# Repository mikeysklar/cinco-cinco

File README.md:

# Cinco-Cinco  
*A 5-Key Wireless Chording Keyboard*

Cinco-Cinco is a low-profile chording keyboard that uses just **five
keys** to emulate a full keyboard by combining keypresses into
chords and utilizing **seven layers**.

I’ve spent the last year building pocket keyboards. My
[BUBBY](https://github.com/mikeysklar/bubby) is a daily carry which
I use for todo lists. It made me enjoy typing with one hand to the
point that I wanted a desktop version, which is what you see here.

## Table of Contents

- [Introduction](#introduction)
- [Hardware Highlights](#hardware-highlights)
  - [Case Design](#case-design)
  - [Mechanical Switch Choice](#mechanical-switch-choice)
  - [Chording Software](#chording-software)
- [CircuitPython Compatibility](#circuitpython-compatibility)
- [Design Files & Software Versions](#design-files--software-versions)
- [Typing Speed](#typing-speed)
- [Layer Maps](#layer-maps)
  - [Layer 1: Letters](#layer-1-letters)
  - [Layer 2: Numbers](#layer-2-numbers)
  - [Layer 3: Whitespace & Delimiters](#layer-3-whitespace--delimiters)
  - [Layer 4: Modifiers & Navigation](#layer-4-modifiers--navigation)
  - [Layer 5: Mouse Control / Media](#layer-5-mouse-control--media)
  - [Layer 6: Media](#layer-6-media)
  - [Layer 7: F1 - F12](#layer-7-F1---F12)
- [BOM](#bill-of-materials)

---

## Introduction

Computing is rapidly changing. We are moving away from sitting at
desks and staring at screens. Smart glasses and watches let us
consume information on the go. Phones, which have taken too much
of our attention, no longer need to be our primary method of
communication.

**The keys are key**

Chording opens up a future of input that is compact, discreet, and
mobile. This same keyboard can also enhance desktop productivity,
allowing CAD users and creatives to use one hand for keyboard
shortcuts while the other handles precise mouse movements.

Cinco-Cinco uses just **five keys**, but can generate over 107
different key combos, including mouse actions. The thumb button
switches between **seven layers**—alphabets, numbers, punctuation,
and more. The layout is based on a modified SAIE layout, optimized so 
the most common letters require minimal finger effort.

At first, I wasn’t sure cramming so much into the thumb key would
work well. But with careful timing and logic in the firmware, it
switches layers smoothly without getting in the way.

---

## Hardware Highlights

- **I2C STEMMA QT connector** for plug-and-play support for different controllers  
- **Two PCB system**: one controller board and one keypad connected via STEMMA QT cable  
- **Hardware-based key detection**: MCP23008 GPIO expander running at 400 kHz for fast, accurate chord detection  
- **BLE-compatible microcontrollers**: Tested with nRF52840  
- **1200mAh battery** integrated into the case to hold keypad in place and reduce charging frequency  

### Case Design

The case is built as a three-layer sandwich. The base has cutouts
to keep components low profile and includes heat-set inserts to
secure the mid and top layers. The PCBs have matching holes for
alignment and locking, ensuring a secure fit.

Flat, countersunk screws keep the top flush. The “Human Machine”
inlay was added late to break up the large pink area and has become
a distinctive feature.

### Mechanical Switch Choice

I chose Kailh PG1350 CHOC switches for their availability and easy
installation. Their low-profile design lets all components fit on
the PCB’s bottom side, simplifying SMT assembly. I’ve tried pink,
red, and robin egg blue switches—the blue ones feel best to type
on, despite needing more force, and they look nice too.

### Chording Software

The firmware works hard to register chords accurately despite early
challenges with false triggers and duplicates. It waits for the
first key release before registering a chord, allowing for sloppy
or staggered key presses without mistakes. It doesn’t wait for all
keys to be released — once a key lifts, the chord buffer clears,
letting you move on quickly.

---

## CircuitPython Compatibility

- **Tested with CircuitPython**: Version 9.2.8
- Library installation process if MacOS is used (delete the ._ libs)

```
circup install adafruit_ble adafruit_bus_device adafruit_hid
cd /Volumes/CIRCUITPY
find . -type f -name '._*' -delete

circup install adafruit_displayio_ssd1306 adafruit_display_text adafruit_ssd1306 adafruit_mcp230xx

cd /Volumes/CIRCUITPY
find . -type f -name '._*' -delete
```

---

## Design Files & Software Versions

### PCB & Schematic Files
- **KiCad**: Version 9

**Cinco-Cinco board (`cinco-cinco/` folder):**
- [`cinco-cinco.kicad_sch`](cinco-cinco/cinco-cinco.kicad_sch)
- [`cinco-cinco.kicad_pcb`](cinco-cinco/cinco-cinco.kicad_pcb)

**nnv2-smd board (`nnv2-smd/` folder):**
- [`nnv2-smd.kicad_sch`](nnv2-smd/nnv2-smd.kicad_sch)
- [`nnv2-smd.kicad_pcb`](nnv2-smd/nnv2-smd.kicad_pcb)

### Case Files (`cad/` folder)
- **FreeCAD**: Version 1.x
- [`case.FCStd`](cad/case.FCStd)

**STL files for 3D printing:**
- [`case-top-cvr.stl`](cad/case-top-cvr.stl)
- [`case-mid-cvr.stl`](cad/case-mid-cvr.stl)
- [`case-lwr-cvr.stl`](cad/case-lwr-cvr.stl)

**STEP files for 3D viewing:**
- [`case-top-cvr.step`](cad/case-top-cvr.step)
- [`case-mid-cvr.step`](cad/case-mid-cvr.step)
- [`case-lwr-cvr.step`](cad/case-lwr-cvr.step)
- [`case-cinco-cinco.step`](cad/case-cinco-cinco.step)
- [`case-bat1200.step`](cad/case-bat1200.step)
- [`case-nnv2-smd.step`](cad/case-nnv2-smd.step)

All hardware design files are open source and located in the `pcb/` and `cad/` directories of this repository.

---

## Typing Speed

Typing speed on the cinco is ~25 WPM. It is fast enough to not be frustrated. Slow enough to improve on.

That is about the same as my typing speed:

* thumb typing speed on my phone
* one handed on a qwerty full size keyboard

---

## Layer Maps

Each layer uses unique key combinations (chords) from the 5 keys (positions 0–4).

| Finger | Key Index |
|:-------|:----------|
| Thumb  | 4         |
| Pinky  | 3         |
| Ring   | 2         |
| Middle | 1         |
| Fore   | 0         |

## Layer 1: Letters 

| Key         | Pky | Rng | Mid | Idx | Thm | Chord         |
|-------------|:---:|:---:|:---:|:---:|:---:|---------------|
| A           |     |  x  |     |     |     | (2,)          |
| B           |  x  |     |     |     |  x  | (3,4)         |
| C           |  x  |     |     |  x  |     | (0,3)         |
| D           |     |  x  |  x  |  x  |     | (0,1,2)       |
| E           |     |     |     |  x  |     | (0,)          |
| F           |     |  x  |  x  |     |  x  | (1,2,4)       |
| G           |     |     |  x  |     |  x  | (1,4)         |
| H           |     |  x  |     |     |  x  | (2,4)         |
| I           |     |     |  x  |     |     | (1,)          |
| J           |     |  x  |  x  |  x  |  x  | (0,1,2,4)     |
| K           |  x  |     |  x  |     |  x  | (1,3,4)       |
| L           |  x  |     |  x  |     |     | (1,3)         |
| M           |     |     |     |  x  |  x  | (0,4)         |
| N           |     |  x  |  x  |     |     | (1,2)         |
| O           |     |  x  |     |  x  |     | (0,2)         |
| P           |  x  |  x  |  x  |     |     | (1,2,3)       |
| Q           |  x  |  x  |  x  |  x  |  x  | (0,1,2,3,4)   |
| R           |     |     |  x  |  x  |     | (0,1)         |
| S           |     |     |     |     |  x  | (3,)          |
| T           |  x  |  x  |     |     |     | (2,3)         |
| U           |  x  |  x  |  x  |  x  |     | (0,1,2,3)     |
| V           |  x  |  x  |     |     |  x  | (2,3,4)       |
| W           |     |  x  |     |  x  |  x  | (0,2,4)       |
| X           |  x  |     |     |  x  |  x  | (0,3,4)       |
| Y           |     |     |  x  |  x  |  x  | (0,1,4)       |
| Z           |  x  |  x  |  x  |     |  x  | (1,2,3,4)     |
| BACKSPACE   |  x  |     |  x  |  x  |     | (0,1,3)       |
| SPACE       |  x  |  x  |     |  x  |     | (0,2,3)       |
    
## Layer 2: Numbers and Arrows 

| Action      | Pky | Rng | Mid | Idx | Thm | Chord           |
|-------------|:---:|:---:|:---:|:---:|:---:|-----------------|
| ONE         |     |     |     |  X  |     | (0,)            |
| TWO         |     |     |  X  |     |     | (1,)            |
| THREE       |     |  X  |     |     |     | (2,)            |
| FOUR        |  X  |     |     |     |     | (3,)            |
| FIVE        |     |     |  X  |  X  |     | (0, 1)          |
| SIX         |     |  X  |  X  |     |     | (1, 2)          |
| SEVEN       |  X  |  X  |     |     |     | (2, 3)          |
| EIGHT       |     |  X  |     |  X  |     | (0, 2)          |
| NINE        |  X  |     |  X  |     |     | (1, 3)          |
| ZERO        |     |  X  |  X  |  X  |     | (0, 1, 2)       |
| UP_ARROW    |     |     |     |  X  |  X  | (0, 4)          |
| DOWN_ARROW  |     |     |  X  |     |  X  | (1, 4)          |
| RIGHT_ARROW |     |  X  |     |     |  X  | (2, 4)          |
| LEFT_ARROW  |  X  |     |     |     |  X  | (3, 4)          |
| PAGE_UP     |     |     |  X  |  X  |  X  | (0, 1, 4)       |
| PAGE_DOWN   |  X  |  X  |     |     |  X  | (2, 3, 4)       |
| END         |     |  X  |  X  |  X  |  X  | (0, 1, 2, 4)    |
| DELETE      |     |  X  |     |  X  |  X  | (0, 2, 4)       |
| INSERT      |  X  |     |  X  |     |  X  | (1, 3, 4)       |
| HOME        |  X  |  X  |  X  |     |  X  | (1, 2, 3, 4)    |

## Layer 3: Whitespace & Delimiters

| Action         | Pky | Rng | Mid | Idx | Thm | Chord         |
| -------------- | :-: | :-: | :-: | :-: | :-: | ------------- |
| ESCAPE         |     |     |     |  X  |     | (0,)          |
| TAB            |     |     |  X  |     |     | (1,)          |
| PERIOD         |     |  X  |     |     |     | (2,)          |
| MINUS          |  X  |     |     |     |     | (3,)          |
| FORWARD_SLASH  |  X  |  X  |     |     |     | (2, 3)        |
| ENTER          |     |     |  X  |  X  |     | (0, 1)        |
| COMMA          |     |  X  |     |  X  |     | (0, 2)        |
| LEFT_BRACKET   |  X  |     |  X  |     |     | (1, 3)        |
| RIGHT_BRACKET  |  X  |     |     |  X  |     | (0, 3)        |
| BACKSLASH      |  X  |  X  |  X  |     |     | (1, 2, 3)     |
| BACKSPACE      |     |  X  |  X  |     |     | (1, 2)        |
| QUOTE          |  X  |     |  X  |  X  |     | (0, 1, 3)     |
| SEMICOLON      |  X  |  X  |     |  X  |     | (0, 2, 3)     |
| GRAVE_ACCENT   |  X  |  X  |  X  |  X  |     | (0, 1, 2, 3)  |
| DELETE         |     |  X  |  X  |  X  |     | (0, 1, 2)     |

## Layer 4: Modifiers & Navigation (SCAG)

| Action         | Pky | Rng | Mid | Idx | Thm | Chord   |
| -------------- | :-: | :-: | :-: | :-: | :-: | ------- |
| LEFT_SHIFT     |  X  |     |     |     |     | (3,)    |
| LEFT_CONTROL   |     |  X  |     |     |     | (2,)    |
| LEFT_ALT       |     |     |  X  |     |     | (1,)    |
| LEFT_GUI       |     |     |     |  X  |     | (0,)    |
| RIGHT_ALT (⌥)  |     |     |  X  |  X  |     | (0, 1)  |

## Layer 5: Mouse Control (Movement, Scroll, Buttons)

| Action         | Pky | Rng | Mid | Idx | Thm | Chord        |
| -------------- | :-: | :-: | :-: | :-: | :-: | ------------ |
| MOVE UP        |     |     |     |  X  |  X  | (0, 4)       |
| MOVE DOWN      |     |     |  X  |     |  X  | (1, 4)       |
| MOVE RIGHT     |     |  X  |     |     |  X  | (2, 4)       |
| MOVE LEFT      |  X  |     |     |     |  X  | (3, 4)       |
| SCROLL UP      |     |     |  X  |  X  |  X  | (0, 1, 4)    |
| SCROLL DOWN    |  X  |  X  |     |     |  X  | (2, 3, 4)    |
| LEFT CLICK     |  X  |  X  |     |     |     | (3, 2)       |
| RIGHT CLICK    |     |     |  X  |  X  |     | (0, 1)       |
| MIDDLE CLICK   |     |     |  X  |     |     | (1, 1)       |
| FORWARD CLICK  |  X  |     |     |  X  |     | (0, 3)       |
| HOLD LEFT      |     |  X  |  X  |  X  |     | (0, 1, 2)    |
| RELEASE LEFT   |  X  |     |  X  |  X  |     | (0, 1, 3)    |
| ACCELERATE     |  X  |  X  |  X  |     |     | (1, 2, 3)    |

## Layer 6: Media

| Action               | Pky | Rng | Mid | Idx | Thm | Chord        |
| -------------------- | :-: | :-: | :-: | :-: | :-: | ------------ |
| BRIGHTNESS_DECREMENT |     |     |     |  X  |     | (0,)         |
| BRIGHTNESS_INCREMENT |     |     |  X  |     |     | (1,)         |
| VOLUME_DECREMENT     |     |  X  |     |     |     | (2,)         |
| VOLUME_INCREMENT     |  X  |     |     |     |     | (3,)         |
| MUTE                 |     |     |  X  |  X  |     | (0, 1)       |
| PLAY_PAUSE           |  X  |  X  |     |     |     | (2, 3)       |
| SCAN_NEXT_TRACK      |     |  X  |     |  X  |     | (0, 2)       |
| SCAN_PREVIOUS_TRACK  |  X  |     |  X  |     |     | (1, 3)       |
| FAST_FORWARD         |  X  |     |     |  X  |     | (0, 3)       |
| REWIND               |     |  X  |  X  |     |     | (1, 2)       |
| STOP                 |     |  X  |  X  |  X  |     | (0, 1, 2)    |
| EJECT                |  X  |     |  X  |  X  |     | (0, 1, 3)    |

## Layer 7: F1 - F12

| Action | Pky | Rng | Mid | Idx | Thm | Chord        |
| ------ | :-: | :-: | :-: | :-: | :-: | ------------ |
| F1     |     |     |     |  X  |     | (0,)         |
| F2     |     |     |  X  |     |     | (1,)         |
| F3     |     |  X  |     |     |     | (2,)         |
| F4     |  X  |     |     |     |     | (3,)         |
| F5     |     |     |  X  |  X  |     | (0, 1)       |
| F6     |     |  X  |  X  |     |     | (1, 2)       |
| F7     |  X  |  X  |     |     |     | (2, 3)       |
| F8     |     |  X  |     |  X  |     | (0, 2)       |
| F9     |  X  |     |  X  |     |     | (1, 3)       |
| F10    |     |  X  |  X  |  X  |     | (0, 1, 2)    |
| F11    |  X  |  X  |  X  |     |     | (1, 2, 3)    |
| F12    |  X  |  X  |     |  X  |     | (0, 2, 3)    |

---

## Bill of Materials

cinco-cinco keypad

| Designators | Qty | Value               | Footprint                 |
|-------------|-----|---------------------|---------------------------|
| R1–R4       | 4   | 10 kΩ               | SMD 0805 resistor         |
| J1          | 1   | Conn_01x04_Socket   | JST-SH 4-pin connector    |
| U1          | 1   | MCP23008-xSS        | SSOP-20 package           |
| SW1–SW5     | 5   | SW_Push             | Kailh PG1350 switch socket|
| JP1         | 1   | SolderJumper_2_Open | 2-pin solder jumper       |

BLE Controller Breakout nRF52840 Nice Nano v2

| Designators | Qty | Value                    | Footprint                 |
|-------------|-----|--------------------------|---------------------------|
| U1          | 1   | Nice!Nano v2             | SuperMini nRF52840        |
| J2          | 1   | Conn_01x04_Socket        | JST-SH 4-pin connector    |
| J1          | 1   | Conn_01x02_Socket        | JST-PH 2-pin connector    |
| SW1         | 1   | SW_SPST                  | SMD slide switch          |

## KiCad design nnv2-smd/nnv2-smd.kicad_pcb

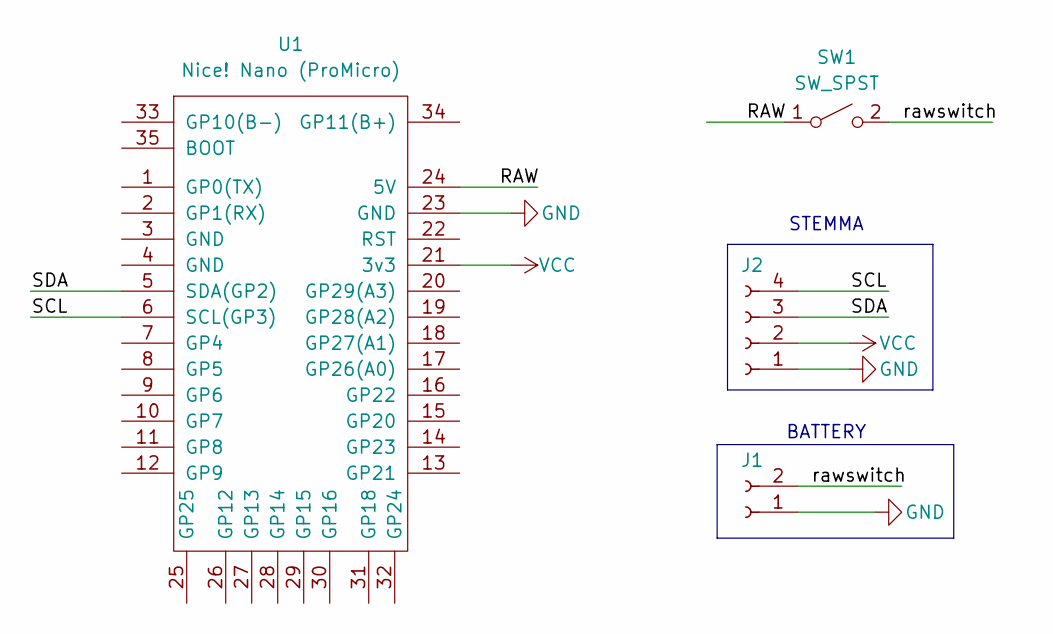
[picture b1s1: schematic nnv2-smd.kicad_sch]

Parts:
J1: Conn_01x02_Socket; JST_PH_S2B-PH-SM4-TB_1x02-1MP_P2.00mm_Horizontal
J2: Conn_01x04_Socket; JST_SH_SM04B-SRSS-TB_1x04-1MP_P1.00mm_Horizontal
SW1: SW_SPST; slide-switch-smd
U1: Nice! Nano (ProMicro); nnv2-mod

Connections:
/RAW: SW1.1 (A), U1.24 (5V)
/SCL: J2.4, U1.6 (SCL(GP3))
/SDA: J2.3, U1.5 (SDA(GP2))
/rawswitch: J1.2, SW1.2 (B)
GND: J1.1, J2.1, U1.23 (GND)
VCC: J2.2, U1.21 (3v3)

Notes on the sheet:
BATTERY
STEMMA

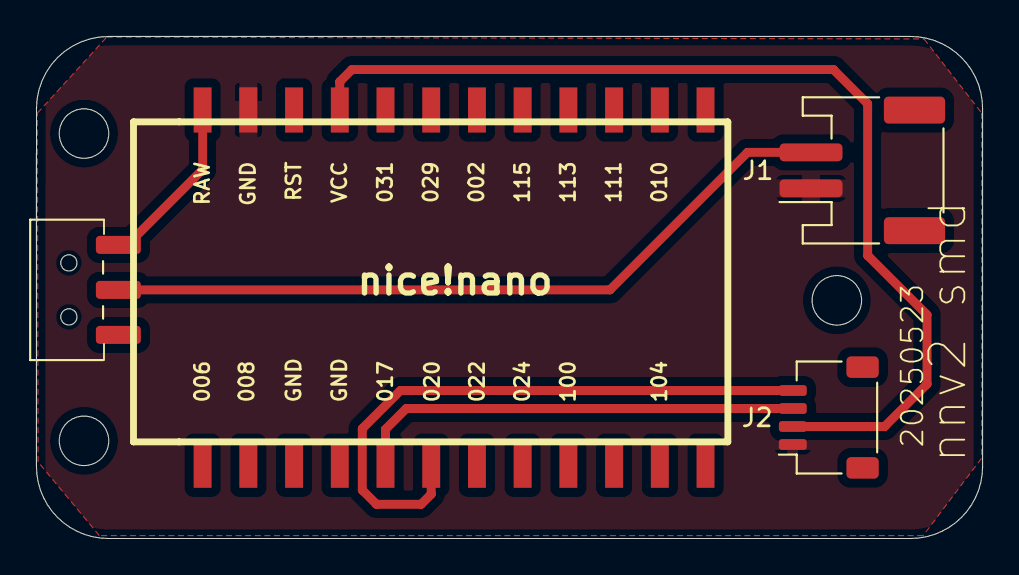
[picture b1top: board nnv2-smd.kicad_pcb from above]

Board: 2 copper layers, 52.6 x 27.9 mm, 4 parts (0 on the bottom side), 6 nets.

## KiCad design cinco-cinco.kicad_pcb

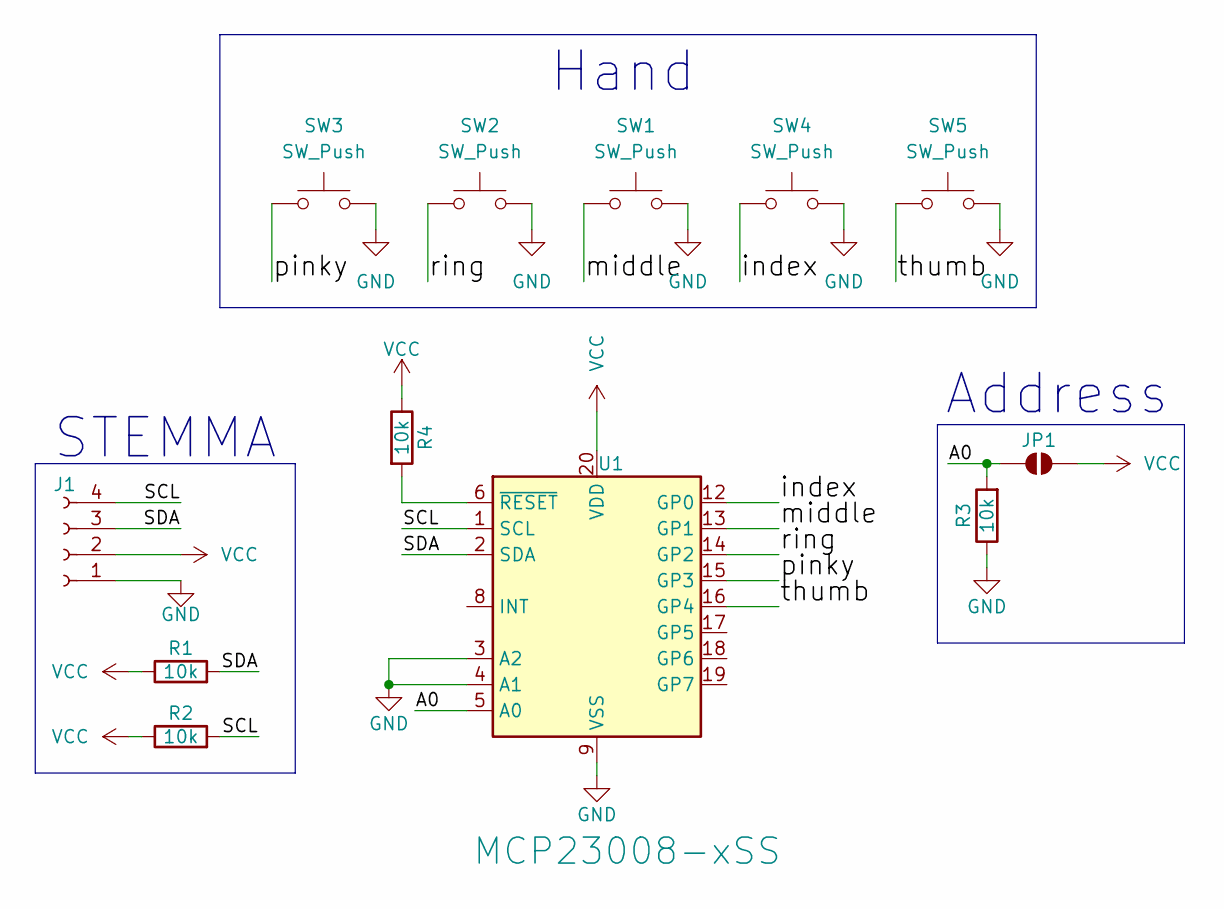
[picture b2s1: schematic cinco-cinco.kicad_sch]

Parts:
J1: Conn_01x04_Socket; JST_SH_SM04B-SRSS-TB_1x04-1MP_P1.00mm_Horizontal
JP1: SolderJumper_2_Open; SolderJumper-2_P1.3mm_Open_TrianglePad1.0x1.5mm
R1, R2, R3, R4: 10k; R_0805_2012Metric_Pad1.20x1.40mm_HandSolder
SW1, SW2, SW3, SW4, SW5: SW_Push; Kailh_socket_PG1350
U1: MCP23008-xSS; SSOP-20_5.3x7.2mm_P0.65mm

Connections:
/A0: JP1.1 (A), R3.2, U1.5 (A0)
/SCL: J1.4, R2.2, U1.1 (SCL)
/SDA: J1.3, R1.2, U1.2 (SDA)
/index: SW4.1, U1.12 (GP0)
/middle: SW1.1, U1.13 (GP1)
/pinky: SW3.1, U1.15 (GP3)
/ring: SW2.1, U1.14 (GP2)
/thumb: SW5.1, U1.16 (GP4)
GND: J1.1, R3.1, SW1.2, SW2.2, SW3.2, SW4.2, SW5.2, U1.3 (A2), U1.4 (A1), U1.9 (VSS)
unnamed: R4.2, U1.6 (~RESET)
VCC: J1.2, JP1.2 (B), R1.1, R2.1, R4.1, U1.20 (VDD)

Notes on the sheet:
STEMMA
Hand
Address

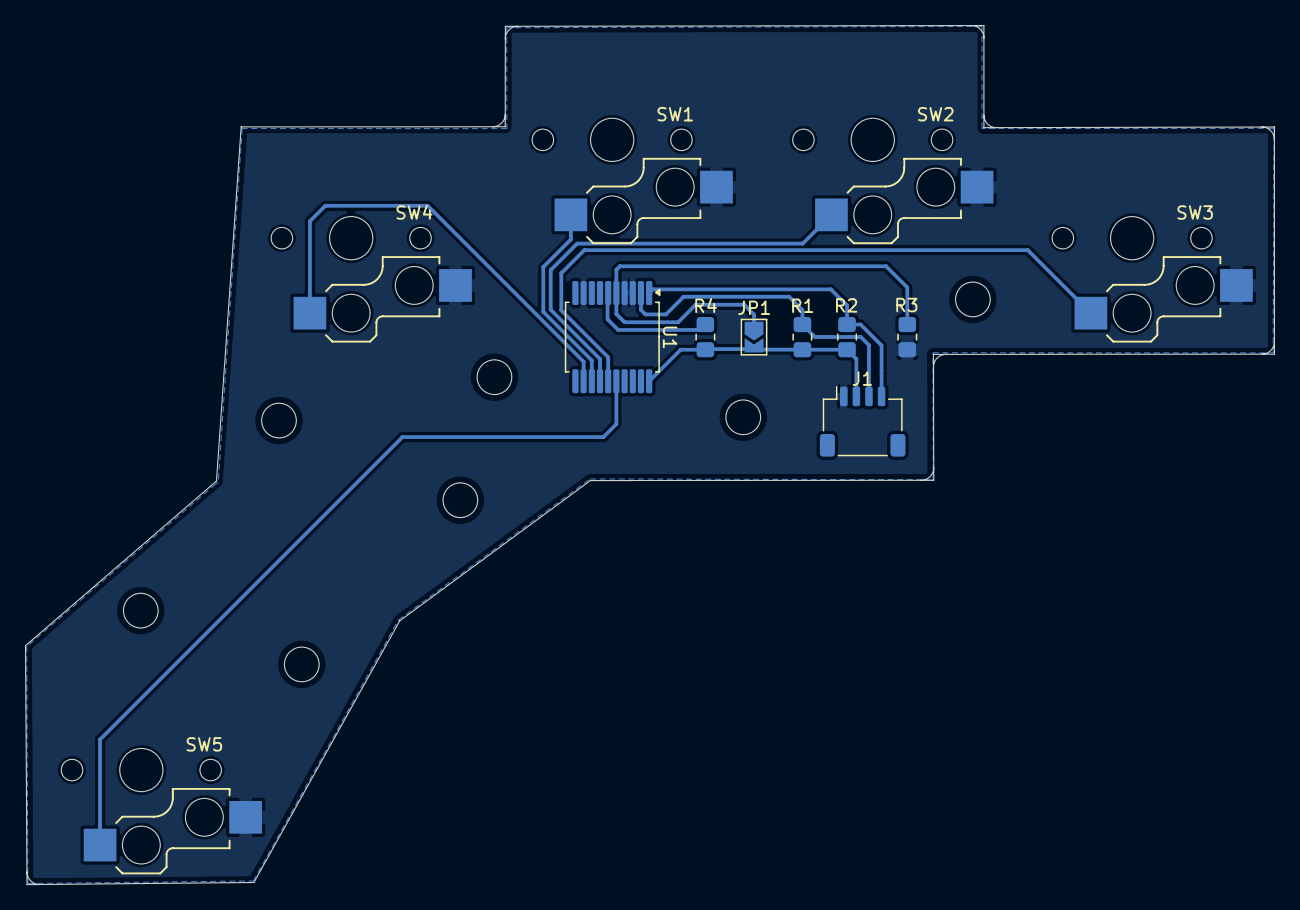
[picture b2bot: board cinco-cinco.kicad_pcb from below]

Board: 2 copper layers, 99.1 x 68.2 mm, 12 parts (7 on the bottom side), 11 nets.

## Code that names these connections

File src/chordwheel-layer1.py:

import matplotlib.pyplot as plt
import numpy as np
from matplotlib.lines import Line2D

# Define finger data and visualization settings
fingers = ['Pinky', 'Ring', 'Middle', 'Index', 'Thumb']
finger_colors = ['#d62728', '#ff7f0e', '#ffdb58', '#2ca02c', '#1f77b4']
finger_markers = ['o', 's', '^', 'D', '*']

# Chord data: fingers pressed per letter (P, R, M, I, T)
chords = {
    'A': [0,1,0,0,0],
    'B': [1,0,0,0,1],
    'C': [1,0,0,1,0],
    'D': [0,1,1,1,0],
    'E': [0,0,1,0,0],
    'F': [0,1,1,0,1],
    'G': [0,0,1,0,1],
    'H': [0,1,0,0,1],
    'I': [0,0,1,0,0],
    'J': [0,1,1,1,1],
    'K': [1,0,1,0,1],
    'L': [1,0,1,0,0],
    'M': [0,0,1,0,1],
    'N': [0,1,1,0,0],
    'O': [0,1,0,1,0],
    'P': [1,1,1,0,0],
    'Q': [1,1,1,1,1],
    'R': [0,0,1,1,0],
    'S': [0,0,0,0,1],
    'T': [1,1,0,0,0],
    'U': [1,1,1,1,0],
    'V': [1,1,0,0,1],
    'W': [0,1,0,1,1],
    'X': [1,0,0,1,1],
    'Y': [0,0,1,1,1],
    'Z': [1,1,1,0,1]
}

num_chords = len(chords)
angle_per_chord = 2 * np.pi / num_chords

fig, ax = plt.subplots(figsize=(10,10), subplot_kw=dict(polar=True))
ax.set_theta_zero_location('N')
ax.set_theta_direction(-1)
ax.set_ylim(0, 7)

ring_radii = [2, 3, 4, 5, 6]

# Draw colored concentric rings
for i, r in enumerate(ring_radii):
    ax.fill_between(np.linspace(0, 2*np.pi, 500), r, r+0.7, 
                    color=finger_colors[i], alpha=0.15)

# Draw radial lines separating wedges
for i in range(num_chords):
    angle = i * angle_per_chord
    ax.plot([angle, angle], [ring_radii[0], ring_radii[-1] + 0.7], color='lightgray', lw=0.8)

# Plot finger dots
for i, (letter, fingers_pressed) in enumerate(chords.items()):
    angle = i * angle_per_chord + angle_per_chord / 2
    for j, pressed in enumerate(fingers_pressed):
        if pressed:
            ax.plot(angle, ring_radii[j] + 0.35, finger_markers[j], markersize=18, 
                    color=finger_colors[j], markeredgecolor='k', markeredgewidth=0.8)

# Letter labels
label_radius = ring_radii[-1] + 1.1
for i, letter in enumerate(chords.keys()):
    angle = i * angle_per_chord + angle_per_chord / 2

    ha = 'center'
    if np.pi / 4 < angle < 3 * np.pi / 4:
        ha = 'center'
    elif 3 * np.pi / 4 <= angle <= 5 * np.pi / 4:
        ha = 'right'
    elif 5 * np.pi / 4 < angle < 7 * np.pi / 4:
        ha = 'center'
    else:
        ha = 'left'

    ax.text(angle, label_radius, letter, fontsize=16, fontweight='bold',
            horizontalalignment=ha, verticalalignment='center')

# Smaller legend/key below the plot
legend_elements = [Line2D([0], [0], marker=m, color='w', label=f, 
                          markerfacecolor=c, markeredgecolor='k', markersize=12, markeredgewidth=0.8) 
                   for m, c, f in zip(finger_markers, finger_colors, fingers)]

ax.legend(handles=legend_elements, loc='lower center', bbox_to_anchor=(0.5, -0.1),
          fontsize=12, frameon=False, ncol=5, title="Fingers")

ax.legend_.get_title().set_fontsize('14')
ax.legend_.get_title().set_fontweight('bold')

ax.grid(False)
ax.set_xticks([])
ax.set_yticks([])

plt.savefig("chord_wheel_clean.svg", format="svg", bbox_inches='tight')
plt.show()

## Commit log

2025-05-21 c5k kicad prototype
2025-05-24 so much new schtuff.
2025-05-26 cad step case
2025-05-28 case / code
    case looks good and went together well..
    code works well first three layers in. locking and fast.
2025-05-29 Update c5k-left.py
    added SCAG modifier keys and mouse layer.
2025-06-07 top cover
    added MCU and BAT covers, lots of room and thick walled 1.6mm
2025-06-10 cleanup / regen design files
2025-06-11 readme
2025-06-11 mark down added
2025-06-11 keycodes
2025-06-11 mouse moves
2025-06-11 mouse moves
    lots of mouse controls.
2025-06-13 sigh...so close
2025-06-14 working out logo stuff
2025-06-14 inlay added
2025-06-14 chart test
2025-06-14 mouse directions code / table
2025-06-14 added some shiznat
2025-06-16 move mouse layer, added nav keys
2025-06-16 updated function keys
2025-06-17 broke out chord map into separate file
2025-06-18 navigation key changes
    * added thumb support to all layers
    * collapsed navigation keys into layer-2
    * added web navigation layer
    * web nav has some issues passing mulitple variables. Need to update code.
    Now Freecad and Kicad layers can be added.
2025-06-19 first 3 layers are good
    checking in before making some larger changes to code setup
2025-06-20 working
    all layers documented, good mouse response.
2025-06-20 focusing on layer-6 media stuff.
2025-06-20 layer-6 sticky
    media keys get stuck due to raw keycdoes going through.
2025-06-23 readme
    bom, re-order readme, write-up
2025-06-24 adding pics
2025-06-24 mov2gif improvements
2025-06-25 readme different angle
2025-06-25 readme done
2025-06-25 hw parts
2025-06-27 svg chordwheels
    layer-1 and layer-2 are good
